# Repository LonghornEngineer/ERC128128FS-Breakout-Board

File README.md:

###ERC128128FS Breakout Board
***
**Quick and dirty breakout board for ERC1281FS LCD Panels**

This repository contains all the documentation and instructions needed for the ERC128128FS Breakout Board.

***
**Directory listing of the repository**

| Directory | Description |
|---|---|
| Hardware | Contains all the hardware files for the Macro_Watch. Designed with Eagle V6.0+. | 
| Software | Has firmware to drive the ERC1281FS. Written in SPIN for the Parallax Propeller. |

***
**Credits**

Designed by:   
Parker Dillmann  

Software by:   
Parker Dillmann  

***

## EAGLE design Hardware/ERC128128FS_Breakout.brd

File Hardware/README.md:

###ERC128128FS Breakout Board
***
**Quick and dirty breakout board for ERC1281FS LCD Panels**

Display can be found [here](http://www.buydisplay.com/default/2-2-inch-serial-i2c-cog-lcd-128x128-graphic-display-module-black-on-white).
J1 is a ER-CON2.0-2P-SMD found [here](http://www.buydisplay.com/default/2-pins-2-0mm-pitch-smd-horizontal-backlight-connector).
J3 is a ER-CON31HT-1 found [here](http://www.buydisplay.com/default/31-pin-0-5mm-pitch-top-contact-zif-connector-fpc-connector).

Display is controlled via I2C.
LCD_BKLT is active low. Pulling it low will enable the backlight. Should be PWM controllable. 

***

***

Files are for Eagle V6.0+. See main directory for licensing.

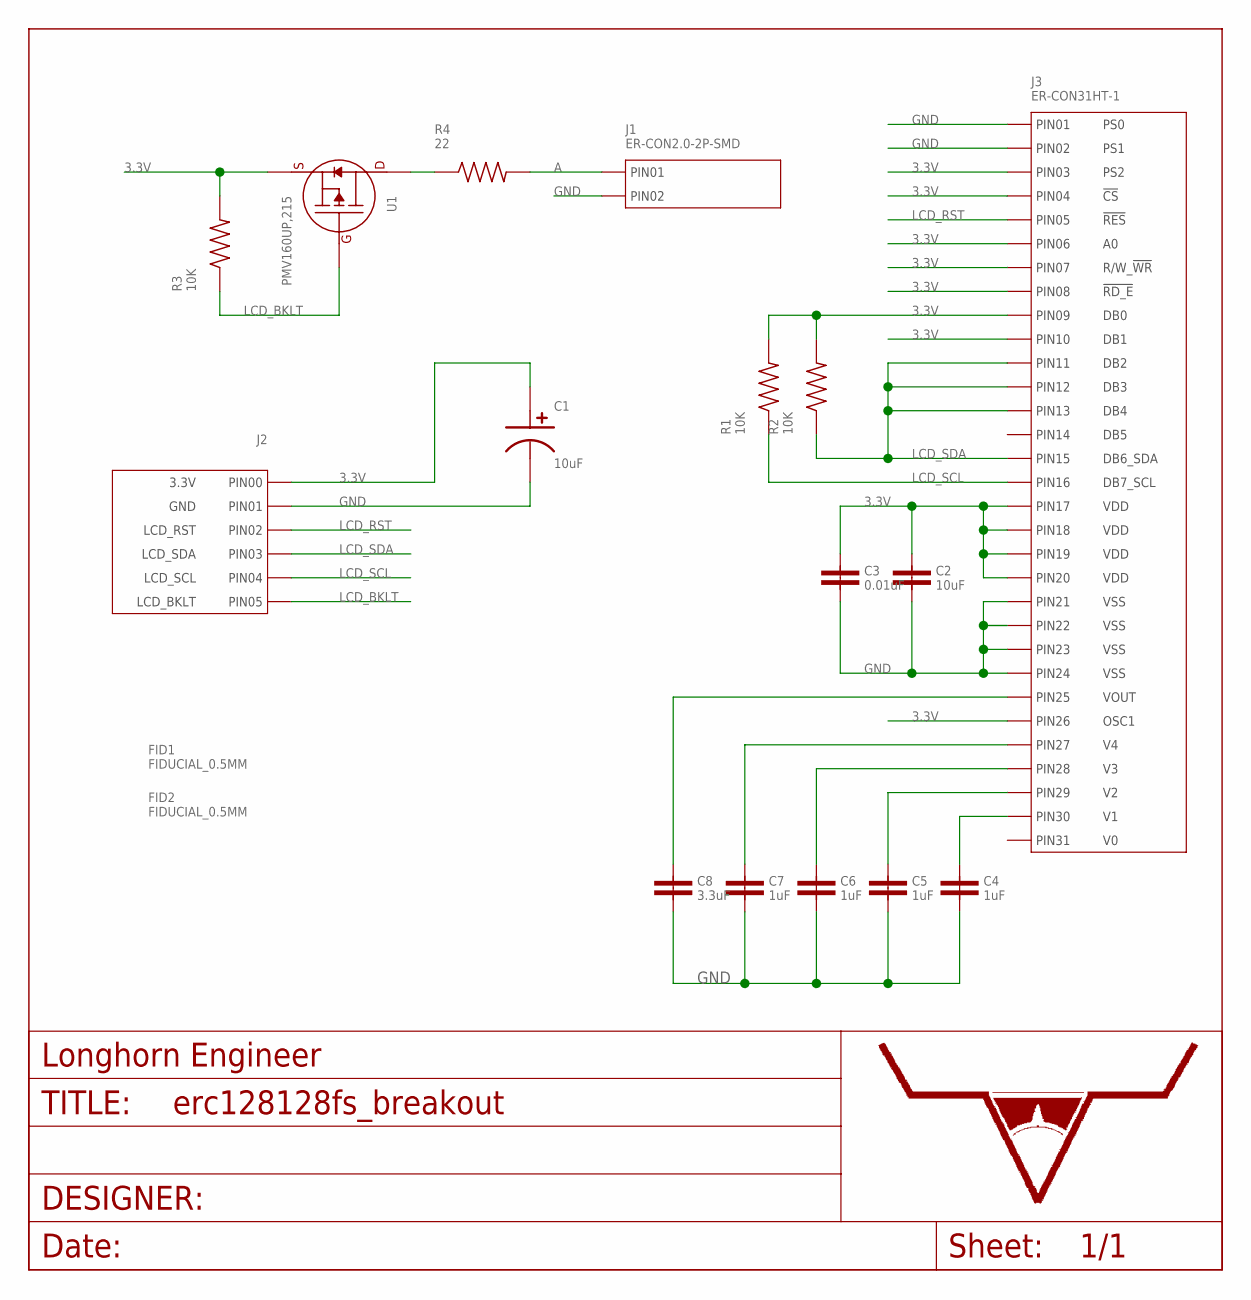
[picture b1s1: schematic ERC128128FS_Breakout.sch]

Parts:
C1: 10uF; CP4MM
C2: 10uF; 1206
C3: 0.01uF; 0603
C4, C5, C6, C7: 1uF; 0603
C8: 3.3uF; 0603
FID1, FID2: FIDUCIAL_0.5MM
J1: ER-CON2.0-2P-SMD
J2: HEADER_01X06_PTH_2.54MM; PTH_2.54MM_01X06
J3: ER-CON31HT-1
R1, R2, R3: 10K; 0603
R4: 22; 0603
U1: PMV160UP,215; SOT-23-3
U$1: LHE_FRAME

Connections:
3.3V: C1.P$1, C2.1, C3.1, J2.P$1 (PIN0), J3.P$3 (PIN3), J3.P$4 (PIN4), J3.P$6 (PIN6), J3.P$7 (PIN7), J3.P$8 (PIN8), J3.P$9 (PIN9), J3.P$10 (PIN10), J3.P$17 (PIN17), J3.P$18 (PIN18), J3.P$19 (PIN19), J3.P$20 (PIN20), J3.P$26 (PIN26), R1.2, R2.2, R3.2, U1.2 (SOURCE)
A: J1.P$1 (PIN1), R4.2
GND: C1.P$2, C2.2, C3.2, C4.2, C5.2, C6.2, C7.2, C8.2, J1.P$2 (PIN2), J2.P$2 (PIN1), J3.P$1 (PIN1), J3.P$2 (PIN2), J3.P$21 (PIN21), J3.P$22 (PIN22), J3.P$23 (PIN23), J3.P$24 (PIN24)
LCD_BKLT: J2.P$6 (PIN5), R3.1, U1.1 (GATE)
LCD_RST: J2.P$3 (PIN2), J3.P$5 (PIN5)
LCD_SCL: J2.P$5 (PIN4), J3.P$16 (PIN16), R1.1
LCD_SDA: J2.P$4 (PIN3), J3.P$11 (PIN11), J3.P$12 (PIN12), J3.P$13 (PIN13), J3.P$15 (PIN15), R2.1
unnamed: R4.1, U1.3 (DRAIN)
unnamed: C8.1, J3.P$25 (PIN25)
unnamed: C7.1, J3.P$27 (PIN27)
unnamed: C6.1, J3.P$28 (PIN28)
unnamed: C5.1, J3.P$29 (PIN29)
unnamed: C4.1, J3.P$30 (PIN30)

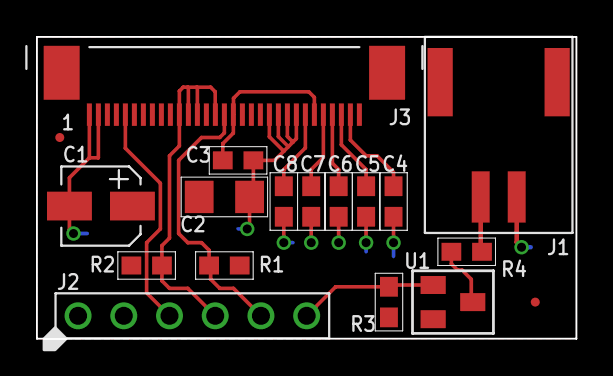
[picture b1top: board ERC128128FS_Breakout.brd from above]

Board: 2 copper layers, 30.0 x 16.8 mm, 19 parts (1 on the bottom side), 13 nets.

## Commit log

2015-11-02 First push of hardware and documentation.
2015-11-02 Tweaked footprint of the FPC
2015-12-14 Updated to new library style.
2016-05-05 Added screen Datasheets.
2016-06-23 Screen functioning!
2016-06-24 Adding screen functions. ASCCI lookup :dancer:
2016-06-25 Upper Caps ASCII table complete
2016-06-27 Basic Library complete.
2016-06-30 Added some Demo Code.

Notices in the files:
parts and their libraries:
PP_Aesthetics: (c) 2015 Longhorn Engineer
